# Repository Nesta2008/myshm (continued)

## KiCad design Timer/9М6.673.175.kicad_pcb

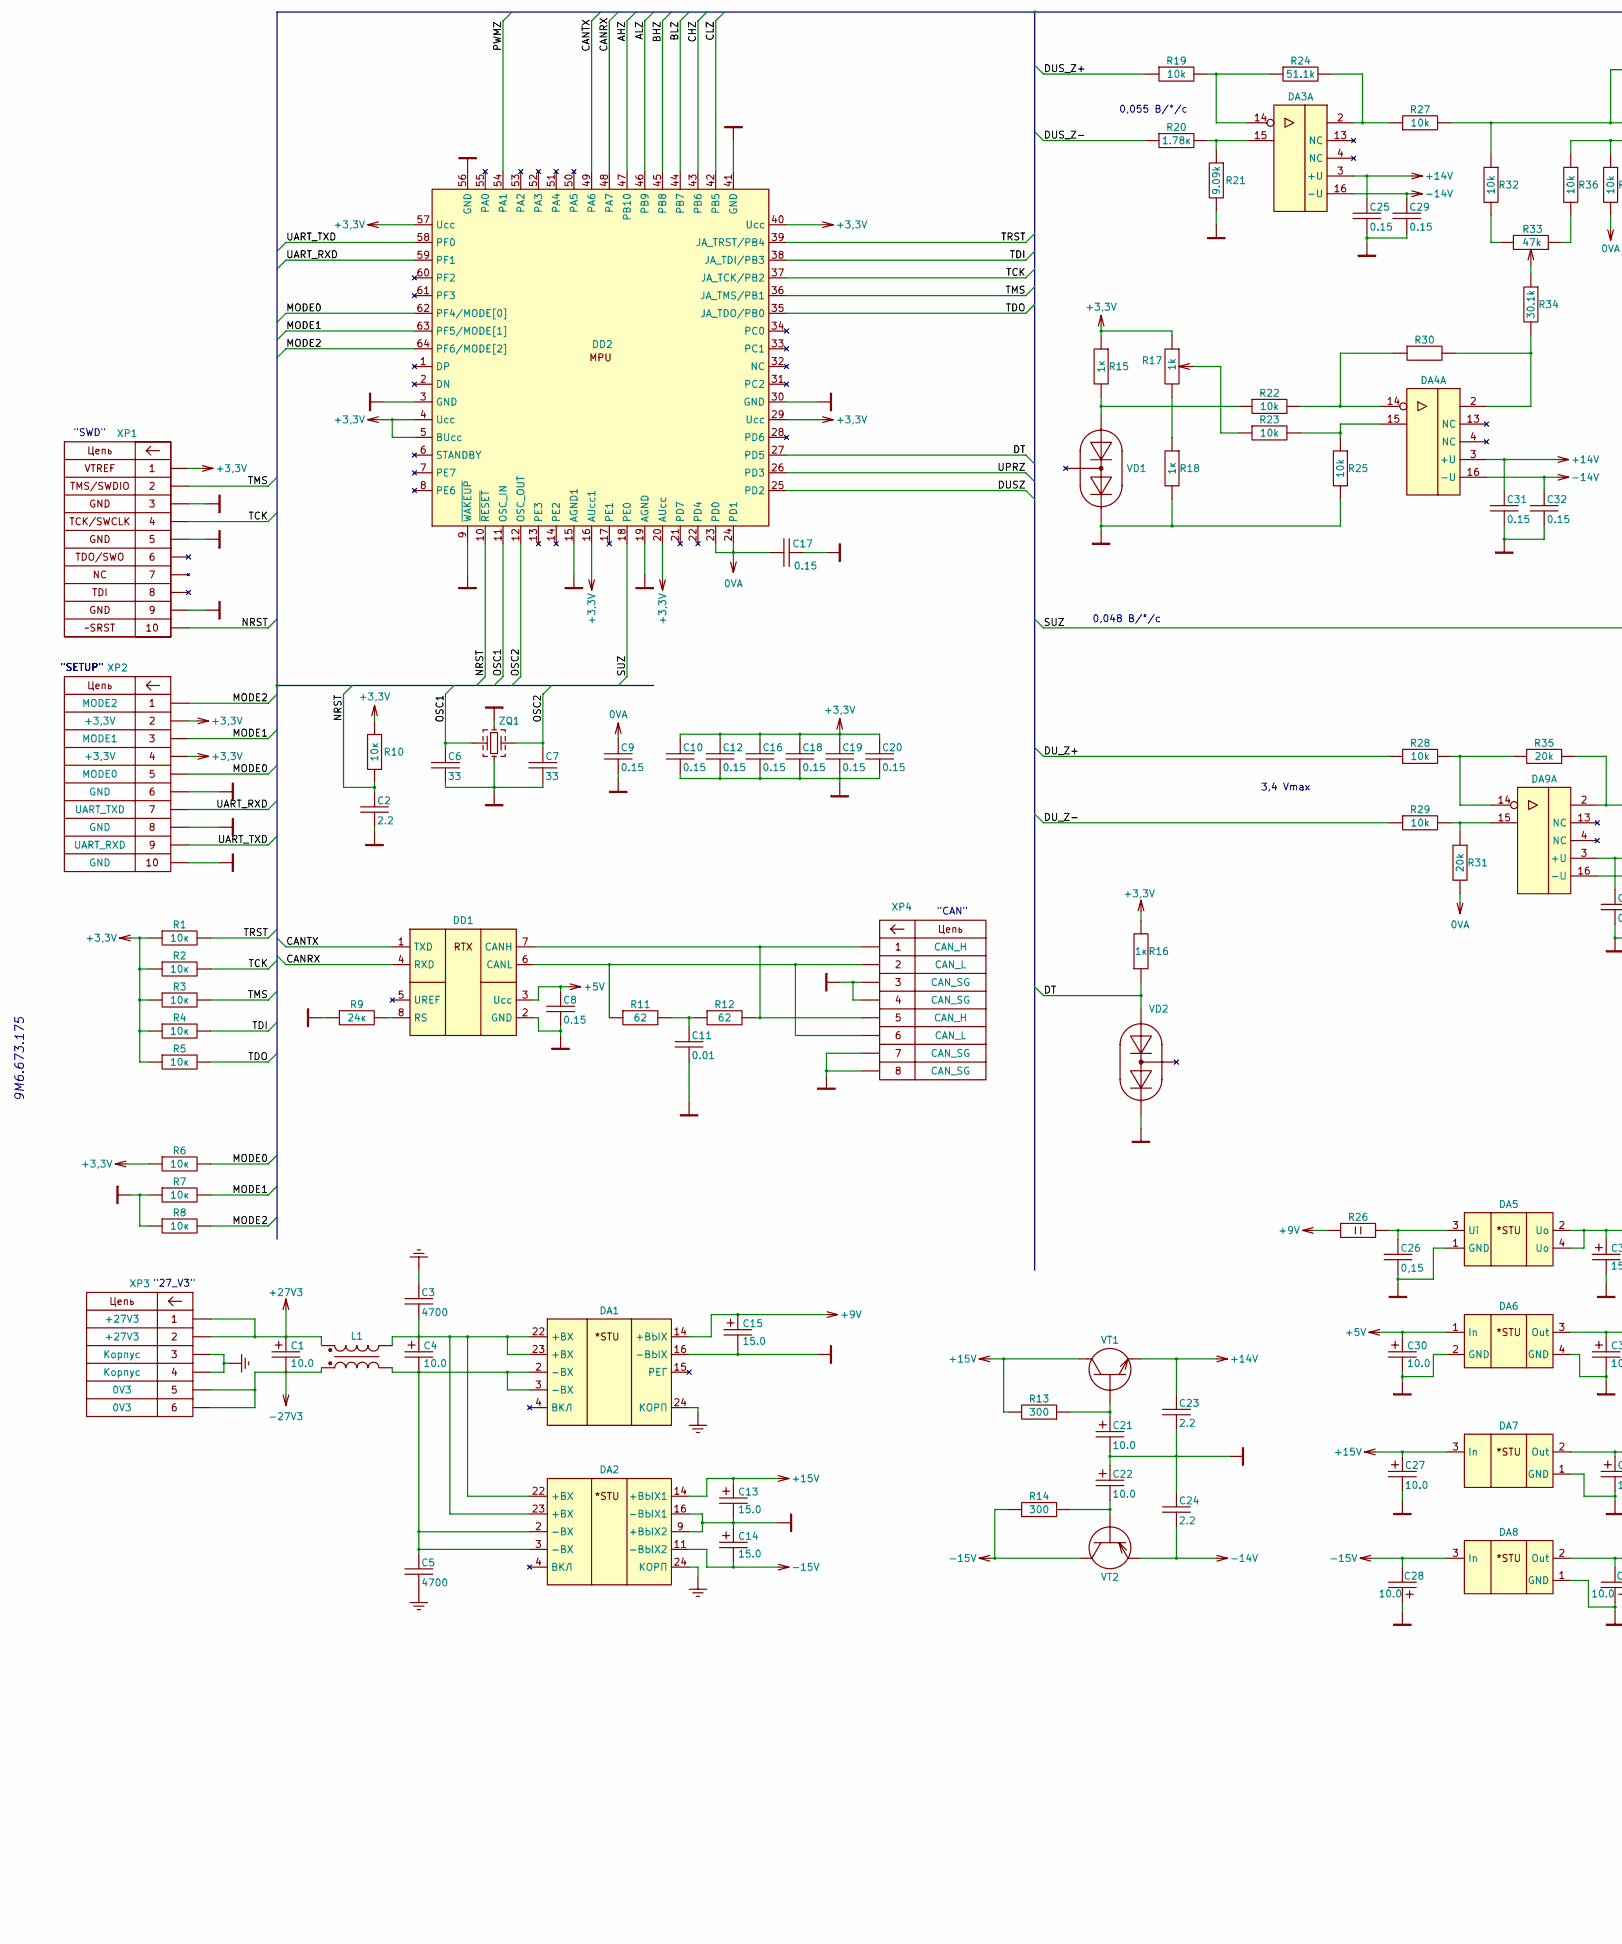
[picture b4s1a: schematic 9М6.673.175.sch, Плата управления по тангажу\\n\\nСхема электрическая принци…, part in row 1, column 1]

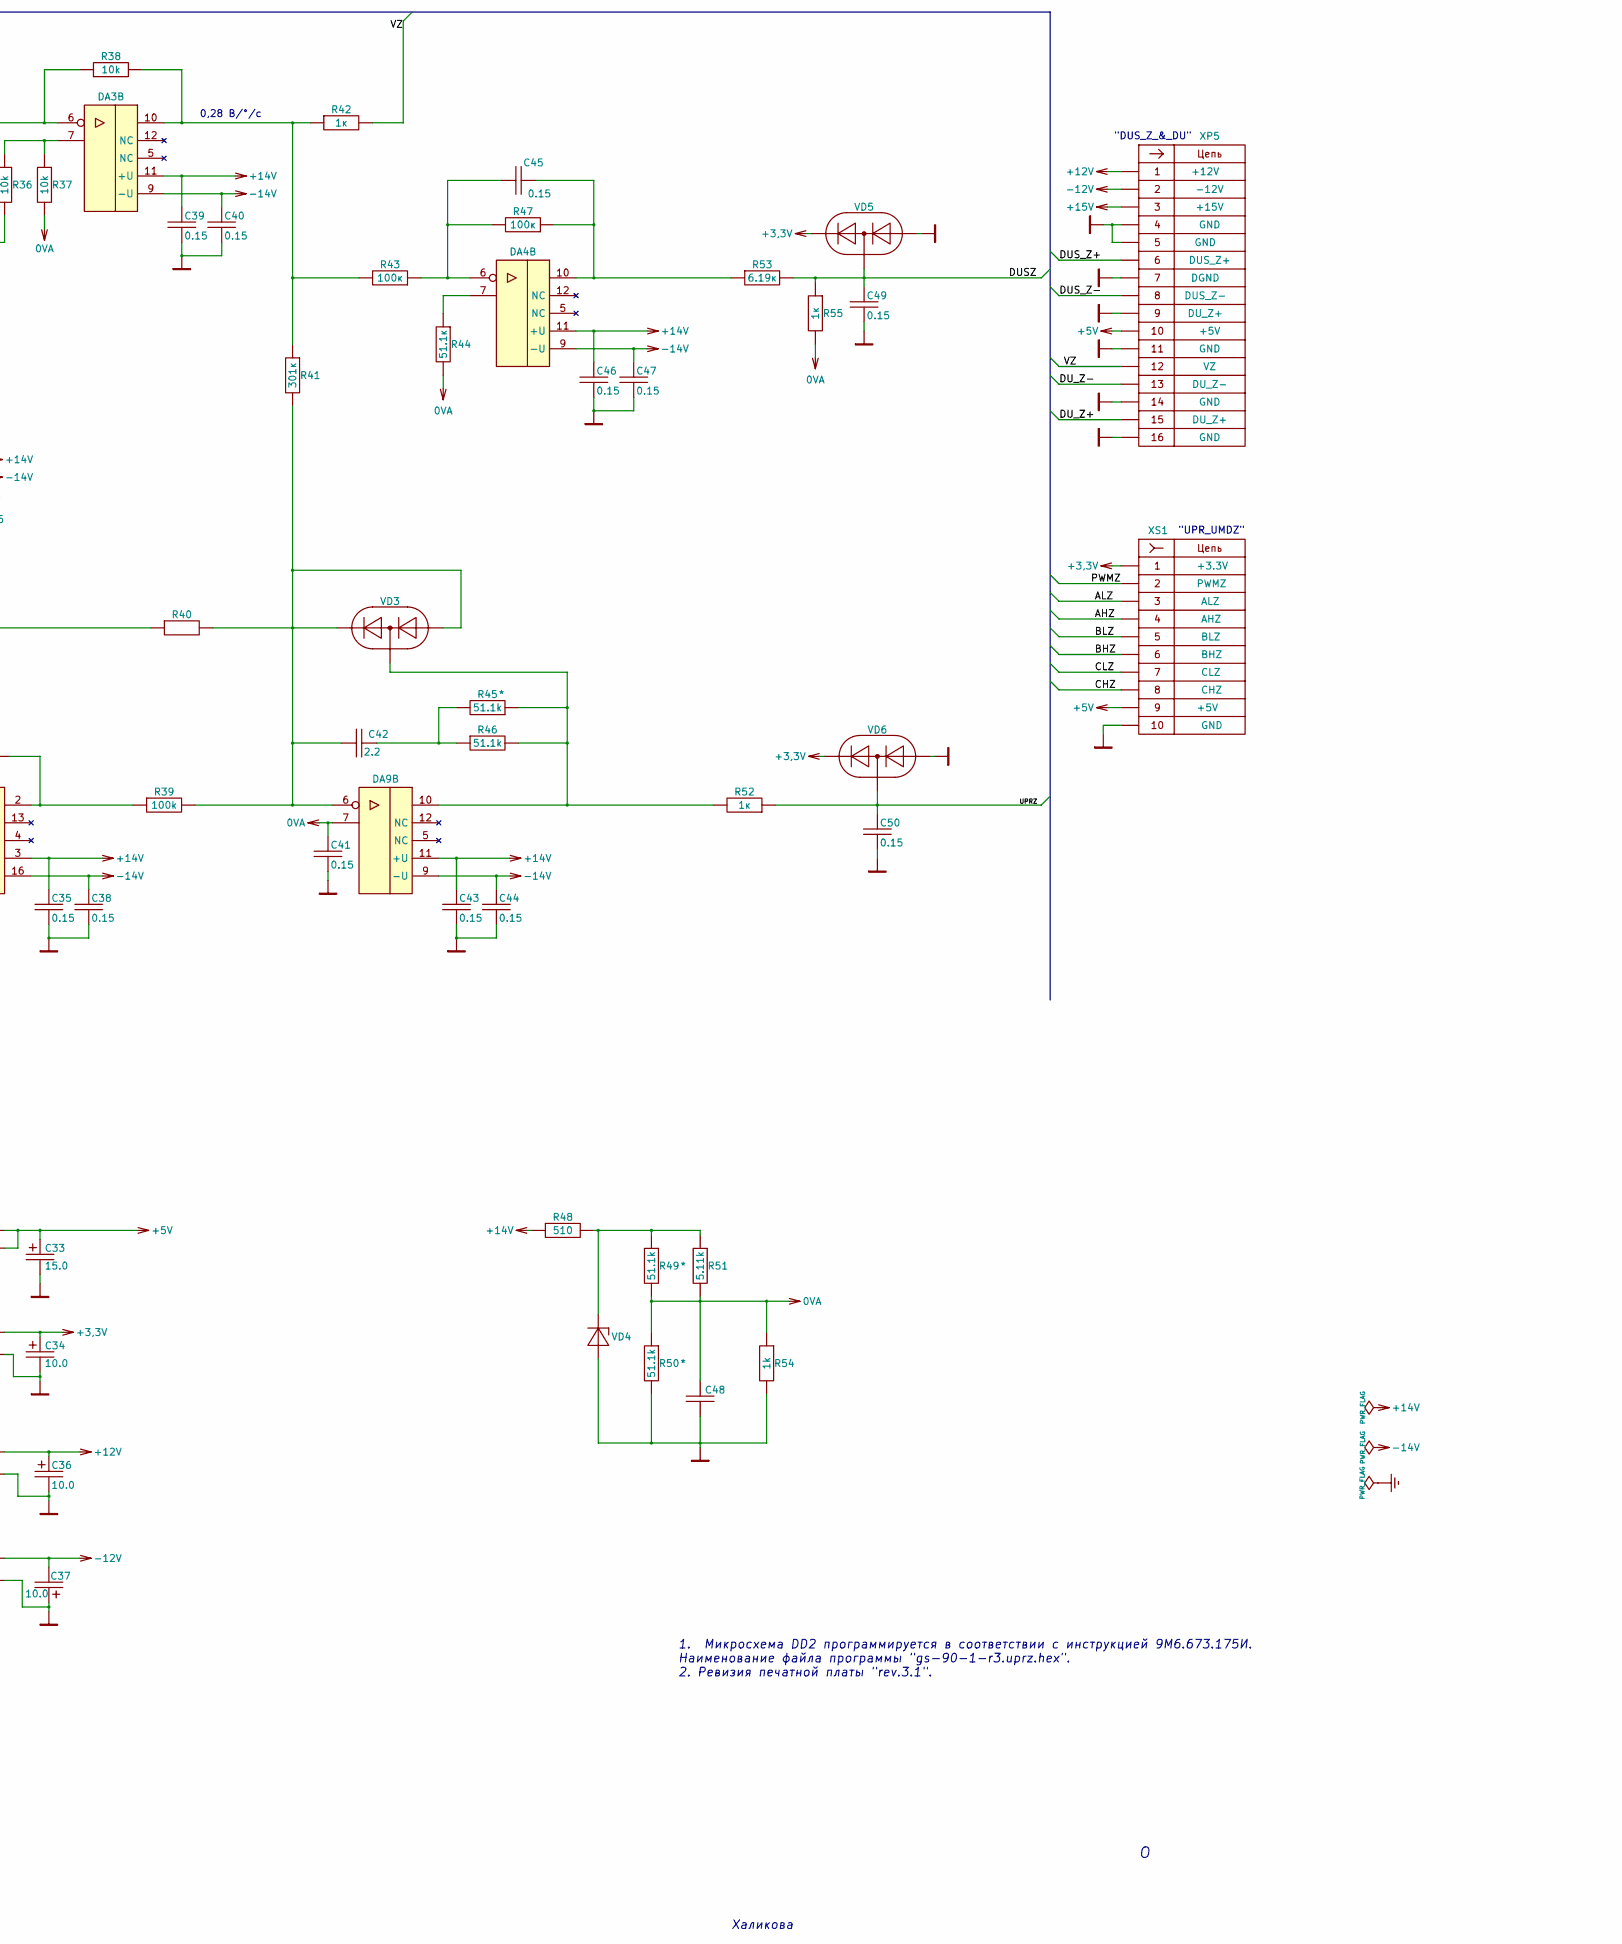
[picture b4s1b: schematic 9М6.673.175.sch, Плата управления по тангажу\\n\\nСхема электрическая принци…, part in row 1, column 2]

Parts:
C1, C4, C30, C34: 10.0; CP_EIA-7343-30_AVX-N
C2, C23, C24, C42: 2.2; C_2220_5650Metric
C3, C5: 4700; C_0805_2012Metric
C6, C7: 33; C_0805_2012Metric
C8, C9, C10, C12, C16, C17, C18, C19, C20, C25, C29, C31, C32, C35, C38, C39, C40, C41, C43, C44, C45, C46, C47, C49, C50: 0.15; C_1206_3216Metric
C11: 0.01; C_1206_3216Metric
C13, C14, C15, C33: 15.0; CP_EIA-7343-30_AVX-N
C21, C22, C27, C28, C36, C37: 10.0; CP_EIA-6032-20_AVX-F
C26, C48: 0,15; C_1206_3216Metric
DA1: Converter_DCDC_AEDON_МДМ8-П_Single_THT
DA2: Converter_DCDC_AEDON_МДМ8-П_Dual_THT
DA3, DA4, DA9: 402.16-23
DA5: КТ-28А-2.02_Horizontal
DA6: TO-252-3_TabPin4
DA7, DA8: KT-93-1
DD1: Н02.8-1В
DD2: 5153.64-2
L1: Choke_ДФПК_7,5-2_0,4
R1, R2, R3, R4, R5, R6, R7, R8, R10: 10к; R_1206_3216Metric
R9: 24к; R_1206_3216Metric
R11, R12: 62; R_1206_3216Metric
R13, R14: 300; R_1206_3216Metric
R15, R16, R18, R42, R52, R55: 1к; R_1206_3216Metric
R17: 1k; СП3-19a2
R19, R22, R23, R25, R27, R28, R29, R30, R32, R36, R37, R38: 10k; R_1206_3216Metric
R20: 1.78к; R_1206_3216Metric
R21: 9.09k; R_1206_3216Metric
R24, R40, R45, R46, R49, R50: 51.1k; R_1206_3216Metric
R26: 5.1; R_4020_10251Metric
R31, R35: 20k; R_1206_3216Metric
R33: 47k; СП3-19a2
R34: 30.1k; R_1206_3216Metric
R39: 100k; R_1206_3216Metric
R41: 301к; R_1206_3216Metric
R43, R47: 100к; R_1206_3216Metric
R44: 51.1к; R_1206_3216Metric
R48: 510; R_1206_3216Metric
R51: 5.11k; R_1206_3216Metric
R53: 6.19к; R_1206_3216Metric
R54: 1k; R_1206_3216Metric
VD1, VD2, VD3, VD5, VD6: SOT-23
VD4: D_КД-2_P10.00mm_Horizontal
VT1, VT2: SOT-89-3
XP1, XP2: PinHeader_2x05_P2.54mm_Vertical
XP3: СНП401-6ВП21-4
XP4: СНП401-8ВП21-4
XP5: СНП401-16ВП21-4
XS1: PinSocket_2x05_P2.54mm_Vertical
ZQ1: Crystal_SMD_7050-4Pin_7.0x5.0mm

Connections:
0VA: C9.1, C17.1, C41.1, C48.1, DA9.7, DD2.23 (PD0), DD2.24 (PD1), R31.2, R37.2, R44.2, R49.2, R50.1, R51.2, R54.1, R55.2
+3,3V: C10.1, C12.1, C16.1, C18.1, C19.1, C20.1, C34.1, DA6.3 (Out), DD2.4 (Ucc), DD2.5 (BUcc), DD2.16 (AUcc1), DD2.20 (AUcc), DD2.29 (Ucc), DD2.40 (Ucc), DD2.57 (Ucc), R1.1, R2.1, R3.1, R4.1, R5.1, R6.1, R10.1, R15.1, R16.2, R17.1, VD5.2 (K), VD6.2 (K), XP1.1, XP2.2, XP2.4, XS1.1
+5V: C8.1, C30.1, C33.1, DA5.2 (Uo), DA5.4 (Uo), DA6.1 (In), DD1.3 (Ucc), XP5.10, XS1.9
+9V: C15.1, DA1.14 (+ВЫХ), R26.1
+12V: C36.1, DA7.2 (Out), XP5.1
+14V: C23.1, C25.1, C31.1, C35.1, C39.1, C43.1, C46.1, DA3.3 (+U), DA3.11 (+U), DA4.3 (+U), DA4.11 (+U), DA9.3 (+U), DA9.11 (+U), R48.1, VT1.3 (E)
+15V: C13.1, C27.1, DA2.14 (+ВЫХ1), DA7.3 (In), R13.2, VT1.2 (C), XP5.3
+27V3: C1.1, L1.3, XP3.1, XP3.2
-12V: C37.2, DA8.2 (Out), XP5.2
-14V: C24.2, C29.1, C32.1, C38.1, C40.1, C44.1, C47.1, DA3.9 (-U), DA3.16 (-U), DA4.9 (-U), DA4.16 (-U), DA9.9 (-U), DA9.16 (-U), VT2.3 (E)
-15V: C14.2, C28.2, DA2.11 (-ВЫХ2), DA8.3 (In), R14.2, VT2.2 (C)
-27V3: C1.2, L1.1, XP3.5, XP3.6
/AHZ: DD2.47 (PB10), XS1.4
/ALZ: DD2.46 (PB9), XS1.3
/BHZ: DD2.45 (PB8), XS1.6
/BLZ: DD2.44 (PB7), XS1.5
/CANRX: DD1.4 (RXD), DD2.48 (PA7)
/CANTX: DD1.1 (TXD), DD2.49 (PA6)
/CHZ: DD2.43 (PB6), XS1.8
/CLZ: DD2.42 (PB5), XS1.7
/DT: DD2.27 (PD5), R16.1, VD2.1 (A)
/DUSZ: C49.1, DD2.25 (PD2), R53.2, R55.1, VD5.3 (common)
/DUS_Z+: R19.1, XP5.6
/DUS_Z-: R20.1, XP5.8
/DU_Z+: R28.1, XP5.15
/DU_Z-: R29.1, XP5.13
/MODE0: DD2.62 (PF4/MODE[0]), R6.2, XP2.5
/MODE1: DD2.63 (PF5/MODE[1]), R7.2, XP2.3
/MODE2: DD2.64 (PF6/MODE[2]), R8.2, XP2.1
/NRST: C2.1, DD2.10 (~RESET), R10.2, XP1.10
/OSC1: C6.1, DD2.11 (OSC_IN), ZQ1.1
/OSC2: C7.1, DD2.12 (OSC_OUT), ZQ1.3
/PWMZ: DD2.54 (PA1), XS1.2
/SUZ: DD2.18 (PE0), R40.1
/TCK: DD2.37 (JA_TCK/PB2), R2.2, XP1.4
/TDI: DD2.38 (JA_TDI/PB3), R4.2
/TDO: DD2.35 (JA_TDO/PB0), R5.2
/TMS: DD2.36 (JA_TMS/PB1), R3.2, XP1.2
/TRST: DD2.39 (JA_TRST/PB4), R1.2
/UART_RXD: DD2.59 (PF1), XP2.7
/UART_TXD: DD2.58 (PF0), XP2.9
/UPRZ: C50.1, DD2.26 (PD3), R52.1, VD6.3 (common)
/VZ: R42.2, XP5.12
Earth: C3.1, C5.2, DA1.24 (КОРП), DA2.24 (КОРП), XP3.3, XP3.4
GND: C2.2, C6.2, C7.2, C8.2, C9.2, C10.2, C11.2, C12.2, C13.2, C14.1, C15.2, C16.2, C17.2, C18.2, C19.2, C20.2, C21.2, C22.1, C23.2, C24.1, C25.2, C26.2, C27.2, C28.1, C29.2, C30.2, C31.2, C32.2, C33.2, C34.2, C35.2, C36.2, C37.1, C38.2, C39.2, C40.2, C41.2, C43.2, C44.2, C46.2, C47.2, C48.2, C49.2, C50.2, DA1.16 (-ВЫХ), DA2.9 (+ВЫХ2), DA2.16 (-ВЫХ1), DA5.1 (GND), DA6.2 (GND), DA6.4 (GND), DA7.1 (GND), DA8.1 (GND), DD1.2 (GND), DD2.3 (GND), DD2.9 (~WAKEUP), DD2.15 (AGND1), DD2.19 (AGND), DD2.30 (GND), DD2.41 (GND), DD2.56 (GND), DD2.65 (GND), R7.1, R8.1, R9.1, R18.2, R21.2, R25.2, R50.2, R54.2, VD1.2 (K), VD2.2 (K), VD4.2 (A), VD5.1 (A), VD6.1 (A), XP1.3, XP1.5, XP1.9, XP2.6, XP2.8, XP2.10, XP4.3, XP4.4, XP4.7, XP4.8, XP5.4, XP5.5, XP5.7, XP5.9, XP5.11, XP5.14, XP5.16, XS1.10, ZQ1.2, ZQ1.4
unnamed: C3.2, C4.1, DA1.22 (+ВХ), DA1.23 (+ВХ), DA2.22 (+ВХ), DA2.23 (+ВХ), L1.4
unnamed: C4.2, C5.1, DA1.2 (-ВХ), DA1.3 (-ВХ), DA2.2 (-ВХ), DA2.3 (-ВХ), L1.2
unnamed: C11.1, R11.2, R12.1
unnamed: C21.1, R13.1, VT1.1 (B)
unnamed: C22.2, R14.1, VT2.1 (B)
unnamed: C26.1, DA5.3 (Ui), R26.2
unnamed: C42.1, R45.2, R46.1
unnamed: C42.2, DA9.6, R39.2, R40.2, R41.2, VD3.1 (A), VD3.2 (K)
unnamed: C45.1, DA4.10, R47.1, R53.1
unnamed: C45.2, DA4.6, R43.1, R47.2
unnamed: DA3.2, R24.2, R27.1
unnamed: DA3.6, R27.2, R32.1, R38.1
unnamed: DA3.7, R36.1, R37.1
unnamed: DA3.10, R38.2, R41.1, R42.1, R43.2
unnamed: DA3.14, R19.2, R24.1
unnamed: DA3.15, R20.2, R21.1
unnamed: DA4.2, R30.2, R34.2
unnamed: DA4.7, R44.1
unnamed: DA4.14, R22.2, R30.1
unnamed: DA4.15, R23.2, R25.1
unnamed: DA9.2, R35.2, R39.1
unnamed: DA9.10, R45.1, R46.2, R52.2, VD3.3 (common)
unnamed: DA9.14, R28.2, R35.1
unnamed: DA9.15, R29.2, R31.1
unnamed: DD1.6 (CANL), R11.1, XP4.2, XP4.6
unnamed: DD1.7 (CANH), R12.2, XP4.1, XP4.5
unnamed: DD1.8 (RS), R9.2
unnamed: R15.2, R22.1, VD1.1 (A)
unnamed: R17.2, R23.1
unnamed: R17.3, R18.1
unnamed: R32.2, R33.3
unnamed: R33.1, R36.2
unnamed: R33.2, R34.1
unnamed: R48.2, R49.1, R51.1, VD4.1 (K)

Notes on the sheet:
Халикова
1. Микросхема DD2 программируется в соответствии с инструкцией 9М6.673.175И. Наименование файла программы "gs-90-1-r3.uprz.hex". 2. Ревизия печатной платы "rev.3.1".
9М6.673.175
"SETUP"
3,4 Vmax
"SWD"
"27_V3"
"CAN"
0,055 В/°/с
"UPR_UMDZ"
0,28 В/°/с
0,048 В/°/с
"DUS_Z_&_DU"

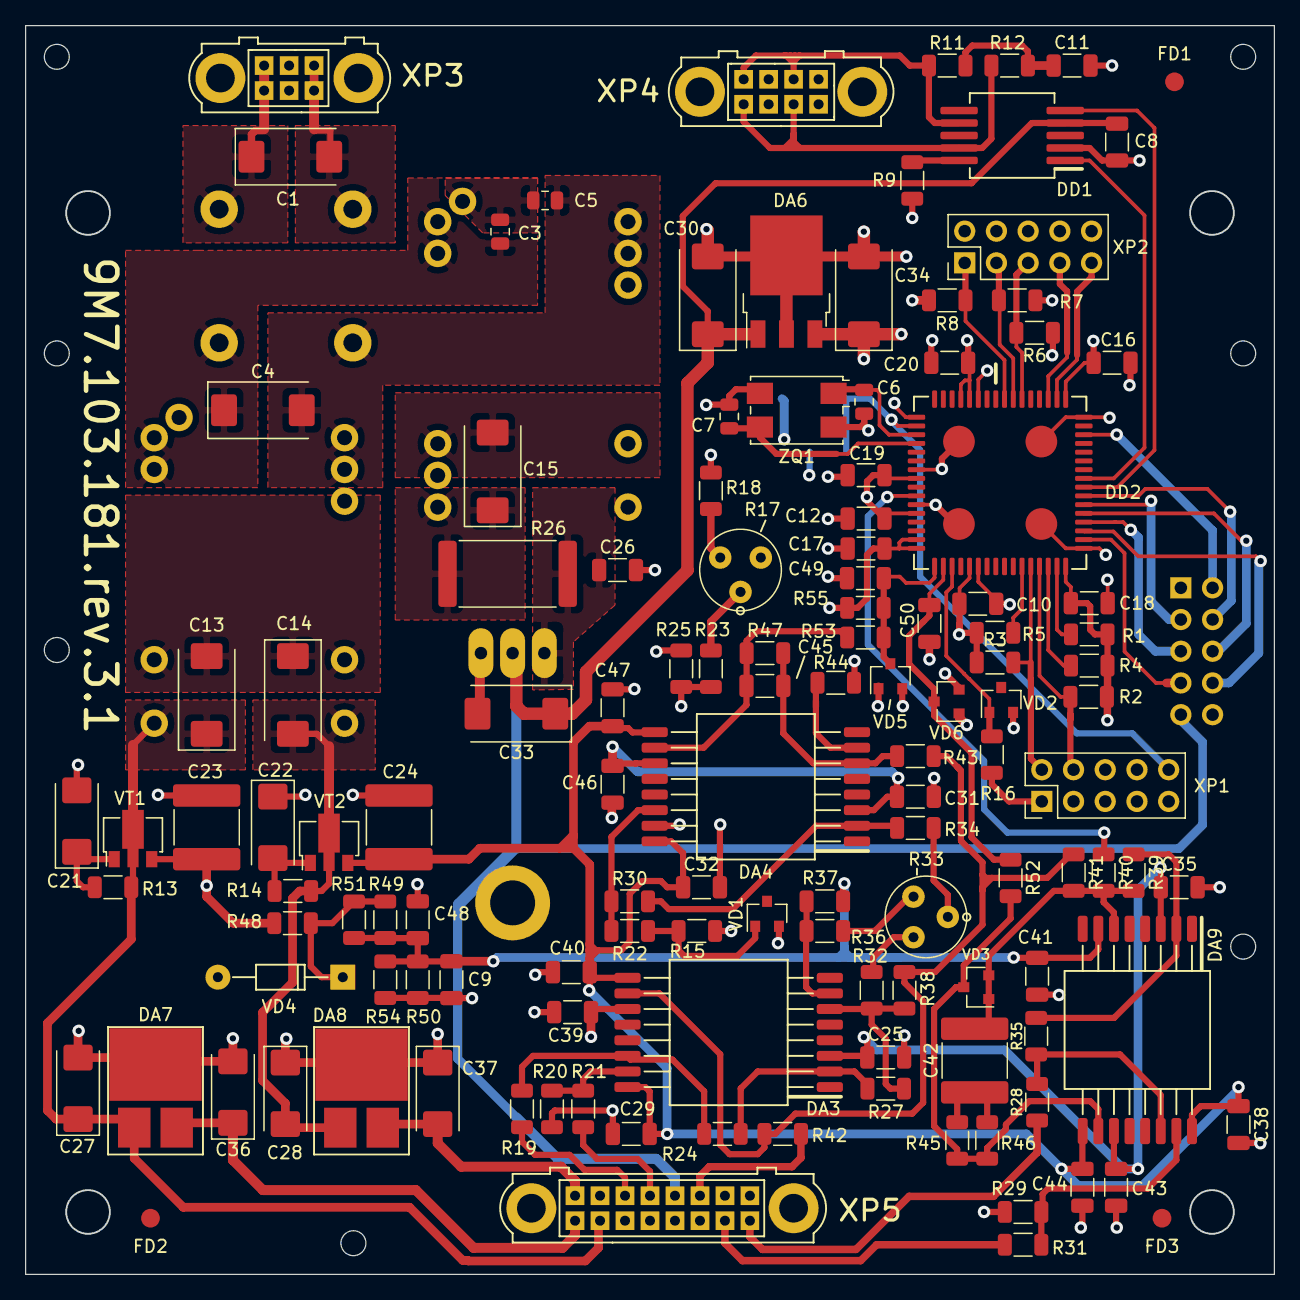
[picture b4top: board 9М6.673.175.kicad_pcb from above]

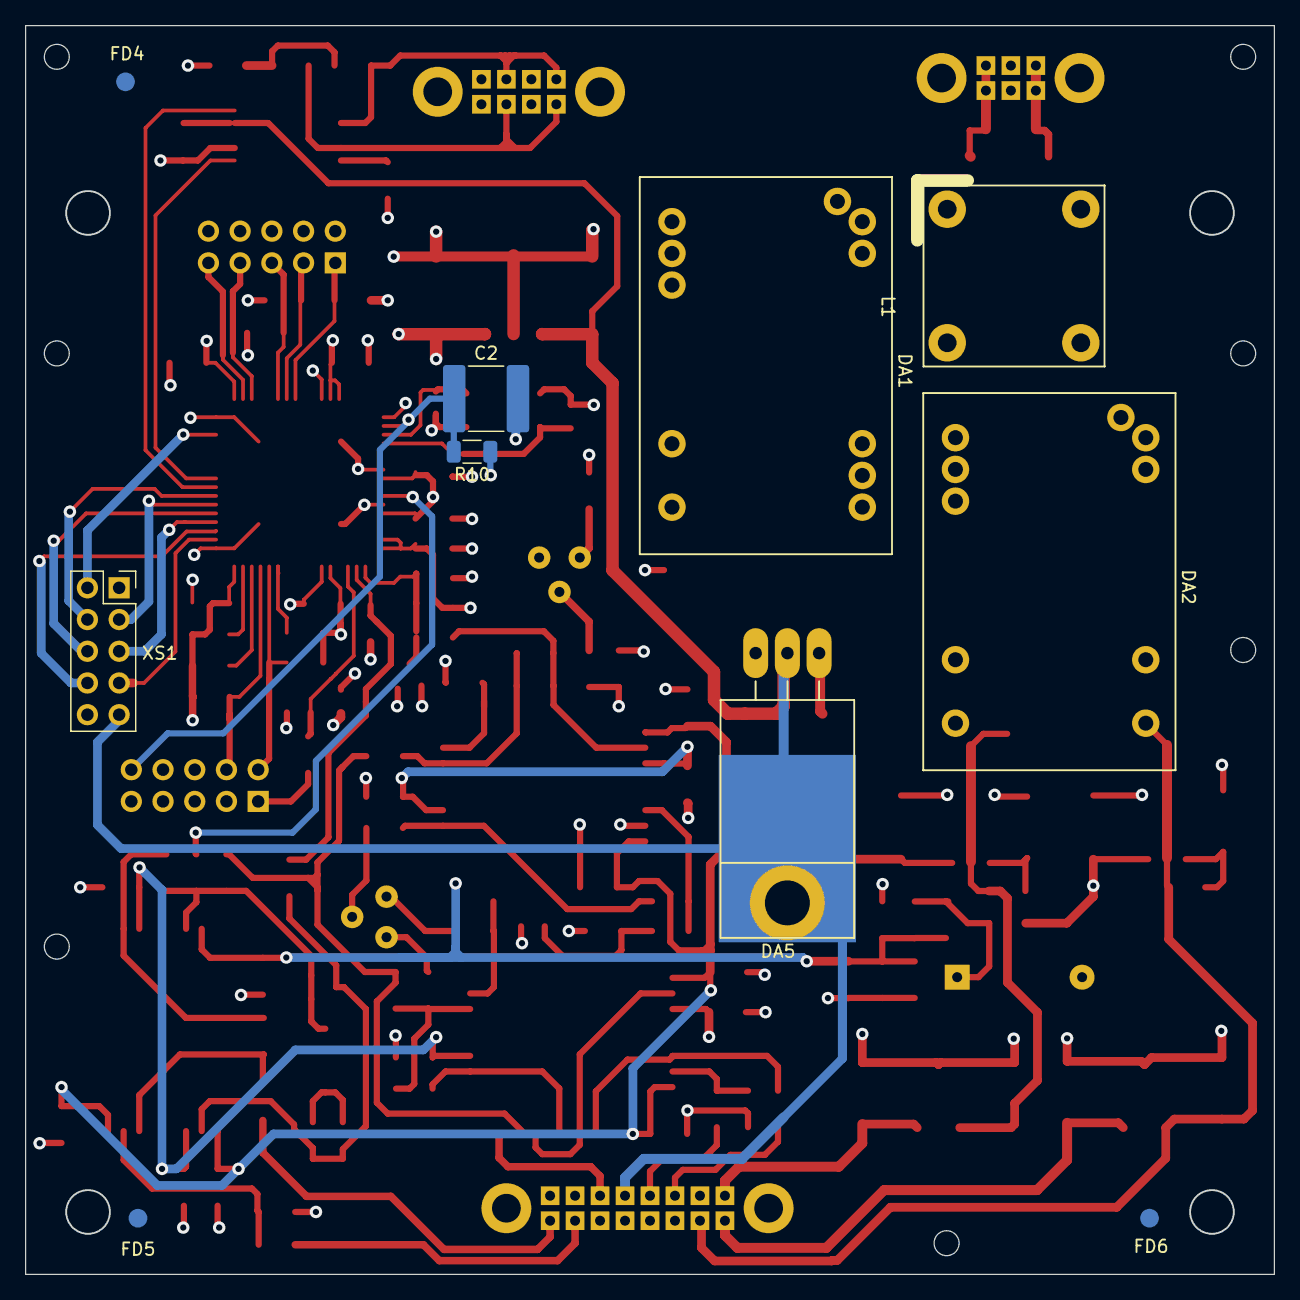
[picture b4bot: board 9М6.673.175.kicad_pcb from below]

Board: 4 copper layers, 100.0 x 100.0 mm, 138 parts (10 on the bottom side), 79 nets.

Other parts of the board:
FD1, FD2, FD3, FD4, FD5, FD6: Fiducial_1.5mm_Mask3mm

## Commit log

2022-06-12 Введены первые исходники
2022-11-03 корректировка Программы в ардуино
2022-11-05 Ввел схемы программаторов
2022-11-06 Ввел трассировку
2024-12-07 Add files via upload
    Коды на СИ
2024-12-07 Add files via upload
    Схемы
2024-12-07 Add files via upload
    Вариант от куратора
2024-12-12 корекктировка кода рекурсии
2024-12-27 Ввел ДЗ по структурам
2025-11-06 Введены новые данные
2025-11-09 Обновлены файлы ЭП
2025-11-29 Timer for STM32
2025-12-28 Схемы ЭП
2026-01-09 Настройка кода с pwm
2026-01-18 Обновил задание по настройке скважности ШИМ по запросу кнопки
